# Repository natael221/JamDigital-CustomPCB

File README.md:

# 🕋 Custom Digital Clock PCB (ESP32 + Arduino Nano)

> A fully integrated, custom PCB redesign of the **Jakarta Dishub Digital Clock**, engineered to eliminate messy jumper wires and deliver a robust, production-ready hardware solution. ⚡

---

## 📸 Hardware Preview

| 📐 Schematic Design | 🖨️ PCB Routing (2D) |
| :---: | :---: |
|  |  |

| 🧊 3D View (Front) | 🧊 3D View (Back) |
| :---: | :---: |
|  |  |

---

## 💡 Overview

This system goes beyond a simple clock. It acts as a real-time information hub displaying **time, date, temperature, humidity, and dynamic motivational quotes** on a **P10 LED Panel**. 

To make it fully autonomous, it features **automatic Adzan audio playback** triggered at specific times via a DFPlayer Mini, all manageable through a **Wi-Fi-based web interface** 🌐.

### 🧠 Dual-Microcontroller Architecture
To handle high-speed display multiplexing without compromising IoT capabilities, the workload is split:
* **ESP32** → The "Brain" handling Wi-Fi, Web Server, sensor polling, and audio logic.
* **Arduino Nano** → The "Display Driver" dedicated entirely to driving the P10 HUB12 panel via I²C commands from the ESP32.

---

## ⚙️ Core Features

* 🕐 **Precision Timekeeping:** Driven by the highly accurate DS3231 RTC module.
* 🌡️ **Environment Monitoring:** Real-time data processing from the DHT22 sensor.
* 🔊 **Automated Audio:** DFPlayer Mini seamlessly plays MP3 files from an SD card.
* 💬 **Dynamic Quotes API:** Fetches and displays daily motivation.
* 🌐 **Local Web Interface:** Easy configuration of settings without hardcoding.
* 🔌 **Custom PCB Design:** Two-layer board integrating all modules flawlessly.

---

## 🎓 The PCB Design Journey

This repository marks my **first dive into designing a PCB from scratch using KiCad 10.0.1**. 

Instead of just wiring modules together, I took the time to understand:
* **Schematic flow and logical groupings.**
* **Netclass configurations** for handling power vs. data lines.
* **Trace routing** with wider tracks for power stability.
* **ERC/DRC validation** to ensure a safe, short-circuit-free design.

> 🎯 *Takeaway: This wasn't just about building a clock; it was a hands-on masterclass in bridging the gap between a messy breadboard prototype and a professional hardware product.*

Check out the original breadboard prototype here: 👉 [Jakarta Dishub Digital Clock v1](https://github.com/natael221/JAMDIGITALPUSDATINDISHUB)

---

## 🧰 Bill of Materials (BOM) Highlights

| Component | Role in the System |
| :--- | :--- |
| **ESP32 Dev Board** | Main IoT Controller |
| **Arduino Nano** | HUB12 Display Controller |
| **P10 LED Panel** | Main Visual Display |
| **DHT22** | Temp & Humidity Sensor |
| **DS3231 RTC** | Real-Time Clock |
| **DFPlayer Mini & Speaker** | Audio Subsystem |

---

## 🚀 Getting Started & Flashing Firmware

1. **Hardware Setup:** Connect both the ESP32 and Arduino Nano to your PC.
2. **Flash ESP32:** Compile and upload `main_esp32.ino` (Target: *ESP32 Dev Module*).
3. **Flash Nano:** Compile and upload `display_nano.ino` (Target: *Arduino Nano*, use Old Bootloader if necessary).
4. **Prepare Audio:** Load your Adzan `.mp3` files into the root/designated folder of a FAT32 formatted SD Card and insert it into the DFPlayer.
5. **Power Up:** Supply a stable **5V DC** to the board. The startup sequence will begin.
6. **Network Config:** Local IP address, connect via your browser, and start configuring! 🎉

---

## 👨‍💻 About the Developer

**Natanael Siwalette** *Embedded Systems | IoT | Hardware Enthusiast*

Currently looking for new opportunities! (Yes, officially unemployed 😢😭, but always building).

📫 **Connect with me:** [LinkedIn](https://www.linkedin.com/in/natanael-siwalette)  
💻 **Check out my work:** [Portfolio](https://natael221.github.io/)

---

## 📜 License

This project is open-source for **educational, research, and prototype development purposes**. Feel free to fork, modify, or use it as inspiration. Proper credit is always appreciated 🙌.

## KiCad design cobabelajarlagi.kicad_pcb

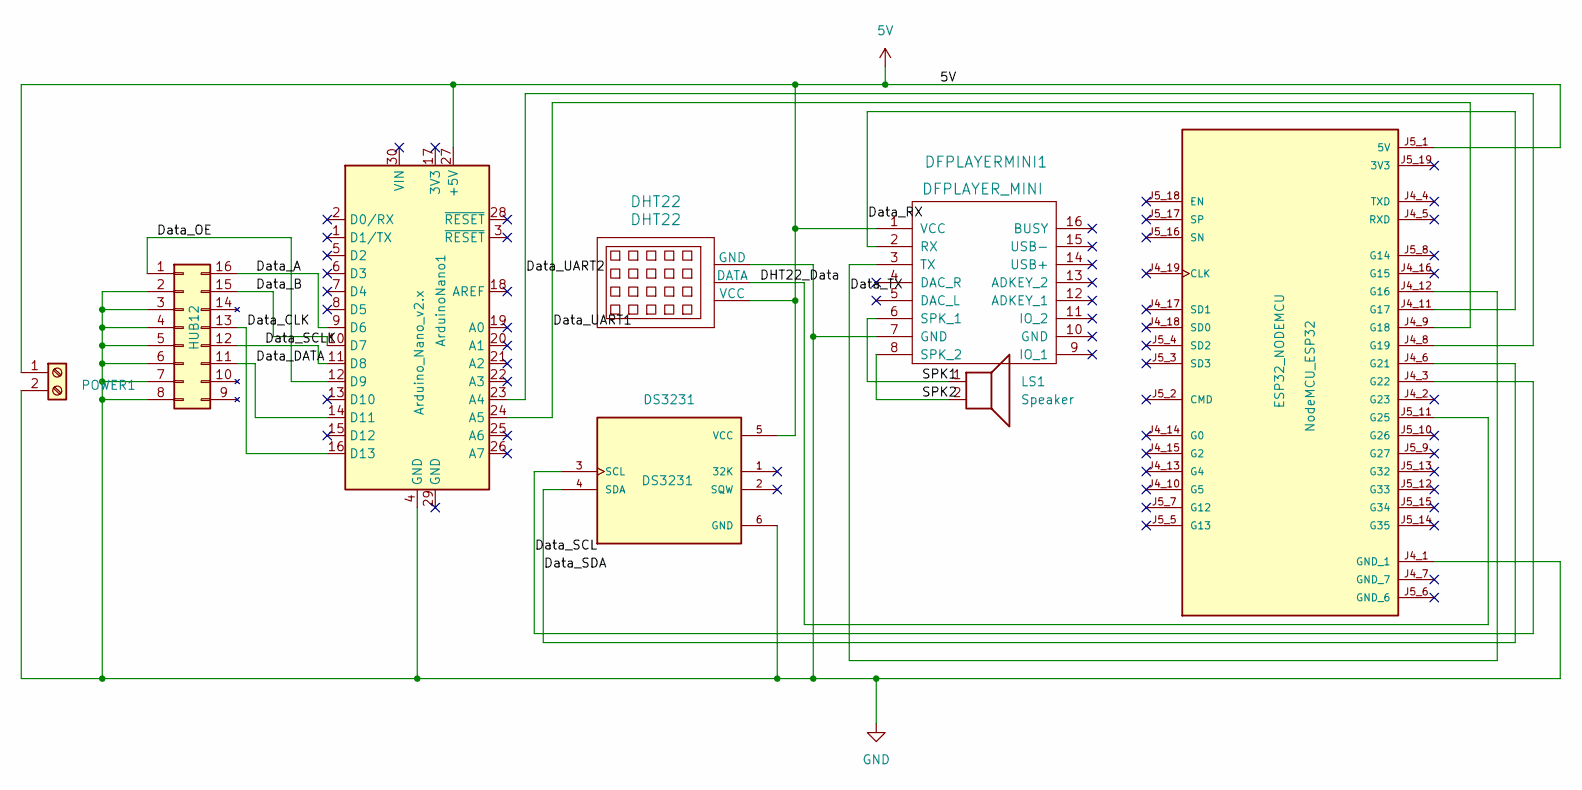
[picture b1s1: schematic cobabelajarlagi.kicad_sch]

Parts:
ArduinoNano1: Arduino_Nano_v2.x; Arduino_Nano
DFPLAYERMINI1: DFPLAYER_MINI; DFPlayer_V2
DHT22: DHT22; DHT11_Temperature_Humidity
DS3231: DS3231; MODULE_TC00500; PARTREV N/A
J1: HUB12; PinHeader_2x08_P2.54mm_Vertical
LS1: Speaker; JST_EH_S2B-EH_1x02_P2.50mm_Horizontal
NodeMCU_ESP32: ESP32_NODEMCU; MODULE_ESP32_NODEMCU
POWER1: POWER; TerminalBlock_Dinkle_DT-55-B01X-02_P10.00mm

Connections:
+5V: ArduinoNano1.27 (+5V), DFPLAYERMINI1.1 (VCC), DHT22.2 (VCC), DS3231.5 (VCC), NodeMCU_ESP32.J5_1 (5V), POWER1.1
/DHT22_Data: DHT22.1 (DATA), NodeMCU_ESP32.J5_11 (G25)
/Data_A: ArduinoNano1.9 (D6), J1.16 (A)
/Data_B: ArduinoNano1.10 (D7), J1.15 (B)
/Data_CLK: ArduinoNano1.16 (D13), J1.13 (CLK)
/Data_DATA: ArduinoNano1.14 (D11), J1.11 (Data)
/Data_OE: ArduinoNano1.12 (D9), J1.1
/Data_RX: DFPLAYERMINI1.2 (RX), NodeMCU_ESP32.J4_11 (G17)
/Data_SCL: DS3231.3 (SCL), NodeMCU_ESP32.J4_3 (G22)
/Data_SCLK: ArduinoNano1.11 (D8), J1.12 (SCLK)
/Data_SDA: DS3231.4 (SDA), NodeMCU_ESP32.J4_6 (G21)
/Data_TX: DFPLAYERMINI1.3 (TX), NodeMCU_ESP32.J4_12 (G16)
/Data_UART1: ArduinoNano1.24 (A5), NodeMCU_ESP32.J4_9 (G18)
/Data_UART2: ArduinoNano1.23 (A4), NodeMCU_ESP32.J4_8 (G19)
/SPK1: DFPLAYERMINI1.6 (SPK_1), LS1.1
/SPK2: DFPLAYERMINI1.8 (SPK_2), LS1.2
GND: ArduinoNano1.4 (GND), DFPLAYERMINI1.7 (GND), DHT22.3 (GND), DS3231.6 (GND), J1.2 (GND), J1.3 (GND), J1.4 (GND), J1.5 (GND), J1.6 (GND), J1.7 (GND), J1.8 (GND), NodeMCU_ESP32.J4_1 (GND_1), POWER1.2

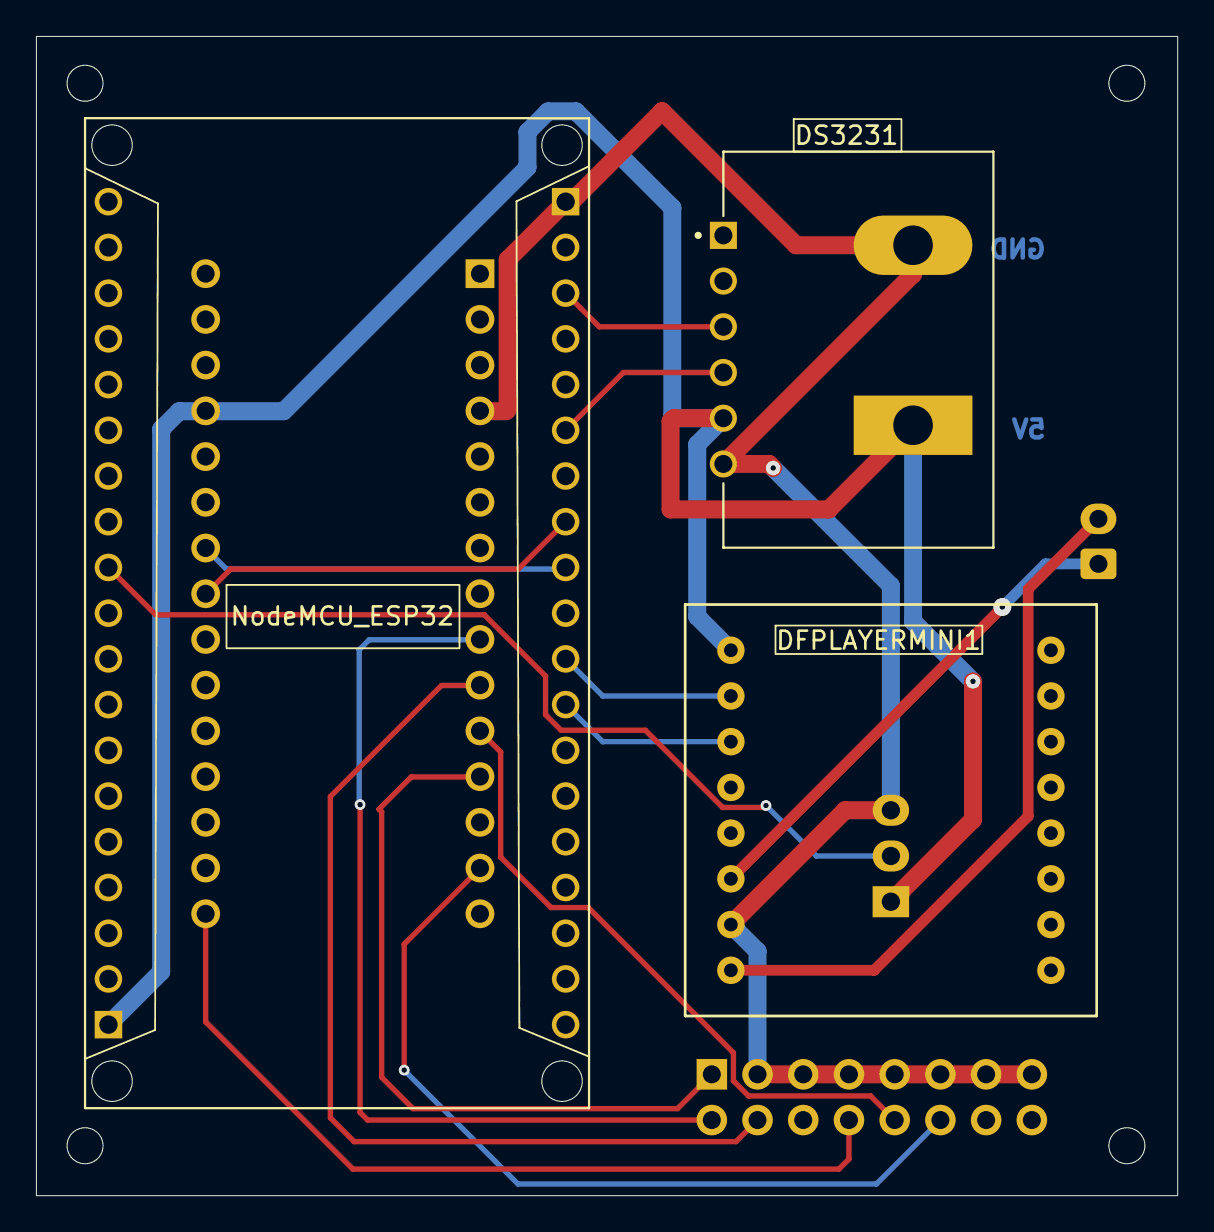
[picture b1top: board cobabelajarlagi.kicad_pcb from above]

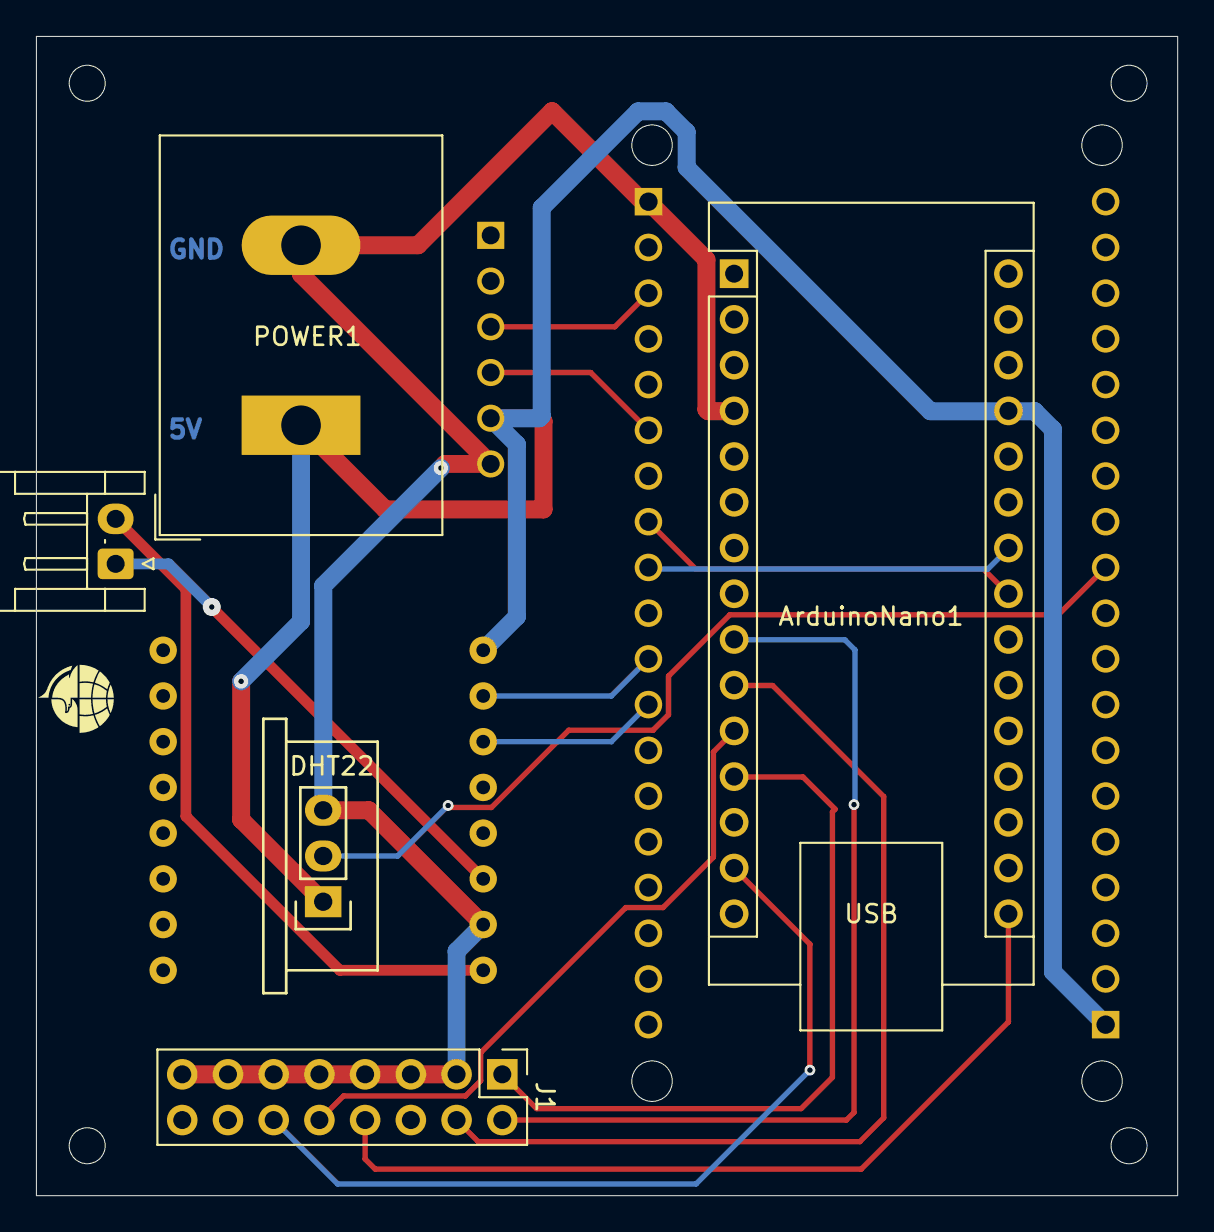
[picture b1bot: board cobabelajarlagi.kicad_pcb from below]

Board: 2 copper layers, 63.4 x 64.4 mm, 8 parts (5 on the bottom side), 17 nets.

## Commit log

2025-10-23 Initial commit: PCB dan schematic Jam Digital Custom
2025-10-24 Update README for clarity and correct employment status
2025-10-24 Fix redundancy in developer section of README
    Removed duplicate 'Unemployed' line from README.
2026-04-26 Revise README for clarity and conciseness
    Updated the README.md to enhance clarity and conciseness in project descriptions, features, and instructions.
2026-04-26 Revise README for improved clarity and organization
    Updated README to enhance structure and clarity, including new sections and images.
2026-04-26 Update network configuration instructions in README
    Simplified the network configuration instruction in the README.
